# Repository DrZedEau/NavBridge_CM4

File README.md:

# NavBridge CM4

A Raspberry Pi Compute Module carrier board for BMW E-Series cars with the factory navigation system (E46, E39, E85 and similar).

The board plugs in between the car harness and the BMW MK3/MK4 navigation module. It brings Android Auto and Apple CarPlay to the factory display, buttons and audio, keeps the factory navigation, and needs no change to the car's wiring. It is made for [NavBridge App](https://github.com/DrZedEau/NavBridge_App), and also runs [LIVI](https://github.com/f-io/LIVI).

## Features

- **Video:** the Pi's picture on the factory display (analog RGB with sync on green), switched with the navigation module's picture from the factory buttons
- **Audio:** USB audio codec, with a stereo line output to the car's AUX or CD changer input and a microphone input
- **I-Bus:** an STM32 between the car and the navigation module turns the Pi on and off with the car, passes the factory buttons to the app and emulates a CD changer. It stays powered from the battery while the Pi is off.
- **Expansion:** two M.2 Key E slots (PCIe + USB, and USB), a USB-C host port for low-power devices (500 mA) and a CSI camera connector
- **CarPlay:** Apple MFi authentication coprocessor
- **Bench use:** a USB-C port to flash the Compute Module and power the board without the car. The MCU is updated from the Pi over USB.
- **Power:** automotive 5 V / 3.5 A buck converter on the fused, TVS-protected battery supply
- 100 × 100 mm, 4-layer PCB

Parts, connectors, pinouts, power and the revision history: [hardware/README.md](hardware/README.md).

## Compute Module

Raspberry Pi **CM4** or **CM5**, with **eMMC** (the board has no SD card slot) and **wireless**. The CM5 boots faster but needs a heatsink.

> [!WARNING]
> A CM4 needs a bootloader setting to turn its 3.3 V rail off at shutdown, otherwise the board keeps drawing from the car battery. See [Compute Module](documentation/README.md#compute-module).

## Documentation

| | |
|---|---|
| [Build and install guides](documentation/README.md) | [Make the navigation cable](documentation/NAV_CABLE.md), [flash the Compute Module](documentation/FLASH.md), [set up the Pi and flash the MCU](documentation/SETUP.md), [install the app](documentation/APP.md), [install in the car](documentation/NAV_CABLE.md#install-in-the-car) |
| [hardware/](hardware/README.md) | KiCad 10 project (revision 0.3), board details, revision history |
| [firmware/](firmware/README.md) | STM32C071 firmware: I-Bus, Pi power, video source, CSYNC, USB bootloader |
| [scripts/](scripts/README.md) | Raspberry Pi setup script and MCU flash script |
| [3D/](3D/README.md) | Printed case and connector housing (not added yet) |
| [images/](images/) | Pictures and renders |

## Project Status

Revision 0.3 adds the USB-C host port and fixes the issues found on the revision 0.2 prototypes, which work in the car with a small I-Bus fix (see [Revision history](hardware/README.md#revision-history)).

- [x] Schematic and PCB layout (revision 0.3)
- [x] Revision 0.2 prototypes built and tested in the car, with a CM4 and a CM5
- [ ] Revision 0.3 prototypes
- [ ] STM32 firmware: first version, being tested on the prototype
- [ ] Raspberry Pi setup script: first version
- [ ] 3D printed case and connector
- [ ] Testing on more BMW models

## Contributing

Bug reports, hardware improvements, firmware and documentation updates are welcome: open an issue or a pull request.

## License

Copyright 2026 DrZedEau

The hardware design — the KiCad project in `hardware/`, the 3D printed parts in `3D/` and the images in `images/` — is licensed under the **CERN Open Hardware Licence Version 2 – Strongly Reciprocal** (CERN-OHL-S-2.0), see [LICENSE](LICENSE). You may redistribute and modify it and make products from it under the terms of that licence. It is distributed without any express or implied warranty, including of merchantability, satisfactory quality and fitness for a particular purpose.

Source location: https://github.com/DrZedEau/NavBridge_CM4

As required by section 4 of the CERN-OHL-S, products made from this design must, where practicable, keep this source location visible.

The firmware in `firmware/` and the Raspberry Pi setup script in `scripts/` are licensed under the **GNU General Public License v2.0** (GPL-2.0), see [firmware/LICENSE](firmware/LICENSE) and [scripts/LICENSE](scripts/LICENSE). Third-party files keep their own licences.

## References

- CM5 NavBridge (previous board) https://github.com/DrZedEau/CM5_NavBridge
- NavBridge App https://github.com/DrZedEau/NavBridge_App
- LIVI project https://github.com/f-io/LIVI
- Raspberry Pi CM4 datasheet https://datasheets.raspberrypi.com/cm4/cm4-datasheet.pdf
- BMW Wiring Diagram System (WDS) https://bmwteka.com/wds/en/e85/e82460cf
- BMW On-Board Monitor documentation https://bmwteka.com/wds/en/e85/1b7f9876
- Community resources https://www.e46fanatics.com/threads/bmw-on-board-monitor-without-navigation-unit.1303552

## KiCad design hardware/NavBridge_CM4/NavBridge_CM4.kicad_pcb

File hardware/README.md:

# Hardware

The NavBridge CM4 board in detail: its parts, connectors, power, video and USB, and the KiCad project.

| Path | Content |
|---|---|
| `NavBridge_CM4/` | Revision 0.3 (current): schematics, PCB layout, project-local symbol, footprint and 3D model libraries |
| `NavBridge_CM4/production/` | JLCPCB fabrication files (Gerber archive, BOM, pick-and-place), made with the Fabrication Toolkit plugin |

Earlier revisions (0.1 and 0.2) are in the git history.

The project was made with **KiCad 10**. Open `NavBridge_CM4/NavBridge_CM4.kicad_pro`.

The project-local libraries only include the 3D models used on the board. The other models come from the standard KiCad library (`KICAD10_3DMODEL_DIR`, and `KICAD9_3DMODEL_DIR` for a few footprints).

## Board

- 100 × 100 mm, 4 copper layers, 1.6 mm
- 4 × M2.5 mounting holes at the corners (3 mm from each edge)
- 4 × M2.5 mounting holes for the Compute Module
- GND stitching vias around the board edge and across the ground pours
- Teardrops on vias and through-hole pads
- The battery fuse holder (FH1) takes a Littelfuse 0451003.MRL (3 A) fuse, fitted by hand after assembly
- No SD card slot: the Compute Module must have eMMC

## Main parts

| Function | Part |
|---|---|
| Compute Module connectors | 2 × Hirose DF40C-100DS (CN1, CN2), CM4 or CM5 |
| MCU | STM32C071 (U9) |
| I-Bus transceivers | 2 × ATA663231: car side (U8), navigation side (U10) |
| 5 V buck, from the car supply | LMR14030-Q1, 5 V / 3.5 A, automotive grade, switched on and off by the MCU |
| Battery protection | Fuse (FH1) and SMCJ24A TVS diode |
| Power muxes | 2 × TPS2117: 5 V from the buck or USB-C (U4), MCU 3.3 V from the LIN regulator or the CM (U11) |
| 3.3 V bucks | 2 × TPS54202, 2 A: USB hub, USB switches and video DAC (U5); M.2 slots and camera (U18) |
| Power switches | 2 × TPS2051B: audio codec; USB-C host port, 500 mA (U15) |
| USB hub | USB2514B, 4 ports |
| USB switches | 2 × TS3USB221: CM USB to the hub or to J1 (rpiboot); hub port 2 to CN6 or to J2 (U14) |
| Video DAC | ADV7125, 24-bit |
| RGB switch | TMUX1574 |
| Audio codec | PCM2912A: stereo line output, mono microphone input with bias |
| CarPlay authentication | Apple MFi343S00177, on I²C |

## Connectors

| Ref | Connector | Use |
|---|---|---|
| CN1, CN2 | Hirose DF40C-100DS | Raspberry Pi CM4 / CM5 |
| CN3 | Molex Micro-Fit 3.0, 12 pins (43045-1200) | To the navigation module |
| CN4 | 2 × 9 pin header, 2.54 mm, right angle | Car harness (X1313 connector) |
| CN5 | 2 × 5 pin header, 1.27 mm | STM32 SWD |
| CN6 | M.2 Key E | PCIe x1 + USB 2.0 module (the USB is shared with J2) |
| CN7 | M.2 Key E | USB 2.0 module |
| U1 | JST GH, 3 pins | Stereo line output |
| U2 | JST GH, 2 pins | Microphone input |
| U20 | 22-pin FPC, 0.5 mm (bottom side) | CSI camera (CAM1, 2 lanes) |
| J1 | USB-C | Raspberry Pi flashing and bench power |
| J2 | USB-C | USB 2.0 host port, 500 mA |

### CN4 – Car harness

| Pin | Signal | Pin | Signal |
|---|---|---|---|
| 1 | +BATT | 2 | GND |
| 3 | – | 4 | – |
| 5 | I-Bus | 6 | GND |
| 7 | – | 8 | – |
| 9 | Green out | 10 | GND |
| 11 | Blue out | 12 | GND |
| 13 | Red out | 14 | GND |
| 15 | – | 16 | – |
| 17 | Nav audio + | 18 | Nav audio − |

### CN3 – Navigation module

| Pin | Signal | Pin | Signal |
|---|---|---|---|
| 1 | GND | 7 | +BATT |
| 2 | GND | 8 | I-Bus (navigation side) |
| 3 | GND | 9 | Red in |
| 4 | GND | 10 | Green in |
| 5 | GND | 11 | Blue in |
| 6 | Nav audio − | 12 | Nav audio + |

+BATT and the navigation audio pass straight through between CN3 and CN4. The I-Bus does not: the car I-Bus (CN4 pin 5) and the navigation module's I-Bus (CN3 pin 8) each have their own ATA663231 transceiver, and the STM32 passes messages between them. The red, green and blue signals from the navigation module go through the RGB switch before reaching the display. The cable from CN3 to the navigation module is in [Make the navigation cable](../documentation/NAV_CABLE.md).

### Audio connectors

| Connector | Pin 1 | Pin 2 | Pin 3 |
|---|---|---|---|
| U2 (microphone) | MIC in | GND | |
| U1 (line out) | Left | GND | Right |

## Buttons and LEDs

| Silkscreen | Part | Function |
|---|---|---|
| nRPIBOOT | SW1 (slide switch) | Pulls the CM `nRPIBOOT` low and routes the CM USB port to the USB-C connector J1, for flashing with rpiboot |
| CN6 / USB-C | SW4 (slide switch) | Connects hub port 2 to M.2 slot CN6 (ON) or to the USB-C host port J2 (OFF) |
| RESET | SW2 | STM32 reset |
| BOOT | SW3 | STM32 BOOT0, to start the USB DFU bootloader |
| PWR | D2 (red) | CM power LED |
| ACT | D1 (green) | CM activity LED |
| STAT | D6 (yellow) | STM32 status LED |

The MCU can only be reflashed with the board powered from USB-C (J1). The BOOT button and the SWD connector's VTref both take their 3.3 V from the Compute Module.

## Power

```text
+BATT ─┬─ fuse ─ TVS ─ LMR14030 5 V buck (enabled by MCU) ─┐
       │                                                   ├─ TPS2117 ─ +5 V ─ CM and peripherals
       │                            USB-C (J1) 5 V ────────┘
       │
       ├─ diode ─ ATA663231 (car I-Bus) ─ 3.3 V ─┐
       │                                         ├─ TPS2117 ─ 3.3 V ─ STM32, RGB switch
       │                  CM 3.3 V output ───────┘
       │
       └─ diode ─ 1 kΩ ─ navigation I-Bus (LIN master termination)

+5 V ─ TPS54202 buck ─ 3.3 V ─ USB hub, USB switches, video DAC (through a ferrite bead)
+5 V ─ TPS54202 buck ─ 3.3 V ─ M.2 slots, camera
+5 V ─ TPS2051B switch ─ PCM2912A audio codec
+5 V ─ TPS2051B switch (500 mA) ─ USB-C host port (J2)
```

- The two TPS54202 converters and the two TPS2051B switches are enabled by the CM 3.3 V output, so they only run while the Compute Module is on.
- The TPS2117 selects between the car supply and USB-C automatically, so the board can be powered on the bench from USB-C alone. A divider on its `PR1` pin makes it switch to the car supply only once the buck output is above about 4.3 V, not while the buck is still starting up. The MCU's TPS2117 does the same with the LIN regulator, above about 2.5 V.
- The MCU is powered from the car battery through the car-side LIN transceiver's built-in 3.3 V regulator, so it keeps watching the I-Bus while the Raspberry Pi is off. It turns the 5 V buck on with the ignition, and off once the CM 3.3 V rail has gone away (see [firmware/README.md](../firmware/README.md)).
- A CM5 under heavy load, together with power-hungry M.2 or USB devices, can get close to the 3.5 A of the 5 V buck.

## I-Bus

- Two **ATA663231** LIN transceivers: one on the car I-Bus (U8), one on the navigation module's I-Bus (U10), with the STM32 in between. It forwards the frames both ways and sends them to the Pi over USB.
- LIN master termination (1 kΩ + diode, R24 and D7) on the navigation-side I-Bus, since the board is the only master on that segment.
- The car's wiring is not modified: the board plugs in between the car harness and the navigation module.

## Video

The Raspberry Pi drives the **ADV7125** video DAC through its 24-bit DPI interface. The STM32 combines the DPI `HSYNC` and `VSYNC` into a composite sync (`CSYNC`) with a hardware timer and feeds it to the DAC, which adds it to the green channel (RGsB) as the BMW display expects. So the board does not rely on the CM5's RP1 PIO for CSYNC, as the [CM5 NavBridge](https://github.com/DrZedEau/CM5_NavBridge) did.

The **TMUX1574** switch, controlled by the STM32, selects which picture reaches the display: the Raspberry Pi or the factory navigation module.

## USB

The CM USB 2.0 port goes through a **TS3USB221** switch controlled by the nRPIBOOT switch (SW1):

- **nRPIBOOT off** (normal use): CM → **USB2514B** hub:
  - port 1: M.2 slot CN7
  - port 2: M.2 slot CN6 or the USB-C host port (J2), through a second **TS3USB221** set by the CN6 / USB-C switch (SW4)
  - port 3: PCM2912A audio codec
  - port 4: STM32
- **nRPIBOOT on**: CM → USB-C connector (J1), to flash the eMMC with rpiboot

The USB-C host port (J2) supplies up to 500 mA through a **TPS2051B** current-limited switch and advertises default USB power (56 kΩ pull-ups on CC1/CC2). It is powered while the Compute Module is on and is meant for low-power devices, such as an analog video converter. When it is selected, M.2 slot CN6 has no USB, only PCIe.

The CM5's USB 3.0 ports are not used.

## Schematic sheets

| Sheet | Content |
|---|---|
| NavBridge_CM4 | CM4 / CM5 connectors, car connectors, audio connectors, LEDs, nRPIBOOT switch, mounting holes |
| Power | Battery input, LMR14030 5 V buck, USB-C connector (J1), TPS2117 power mux, TPS54202 3.3 V buck for the USB hub, the USB switches and the video DAC |
| MCU_Lin | STM32C071 MCU, two ATA663231 LIN transceivers (car I-Bus and navigation I-Bus), navigation I-Bus master termination, TPS2117 MCU power mux, SWD connector |
| Analog_RGB | ADV7125 video DAC and its supply filter, TMUX1574 RGB switch, 75 Ω termination |
| USB | USB2514B hub, TS3USB221 USB switch for rpiboot |
| USB-DFP | USB-C host port (J2), TS3USB221 switch between M.2 slot CN6 and J2 (set by SW4), TPS2051B 500 mA VBUS switch |
| Audio | PCM2912A USB audio codec and its power switch |
| M.2 | Two M.2 Key E slots, TPS54202 3.3 V buck |
| Misc | Apple MFi authentication coprocessor, CSI camera connector |
| SD_Card | Empty: the SD card slot was removed in revision 0.2 |

## Revision history

### 0.3 (current)

Not built yet. Changes from revision 0.2:

- **USB-C host port (J2)**, on the new USB-DFP sheet. A TS3USB221 (U14), set by the CN6 / USB-C slide switch (SW4), connects hub port 2 either to M.2 slot CN6 or to J2. VBUS comes from a TPS2051B (U15, 500 mA, on while the Compute Module is on), and 56 kΩ pull-ups on CC1/CC2 (R32, R33) advertise default USB power. The port is meant for low-power devices, such as an analog video converter.
- **3.3 V for the USB hub, the USB switches and the video DAC** now comes from a TPS54202 buck (U5) instead of the TLV75533 LDO.
- **M.2 3.3 V buck:** TPS54202 (U18) instead of the AP63203.
- **Video DAC supply:** an extra 22 µF after the ferrite bead, which lowers and damps the resonance of the bead and capacitor filter.
- **Navigation I-Bus master termination** on the board: D7 (1N4148W) and R24 (1 kΩ, 1206) from +BATT to IBUS_NAV, next to U10. This replaces the revision 0.2 bodge (see below).
- **MCU power mux (U11):** R25 (150 kΩ) and R26 (100 kΩ) divide `+3V3_LIN_REG` onto `PR1`, so U11 only selects the LIN regulator above about 2.5 V (see below).
- **Main power mux (U4):** R10 (330 kΩ) and R11 (100 kΩ) divide `+5V_BUCK` onto `PR1`, so U4 only switches to the car supply once the buck output is above about 4.3 V. With `PR1` tied straight to `VIN1`, as on revision 0.2, and USB-C and the car supply both connected, U4 would switch to the buck at about 1 V while it starts up, and stay on it while it decays at turn-off.
- **BOOT button (SW3):** now pulls BOOT0 up from the CM 3.3 V rail (`+3V3`) instead of the MCU rail (`+3V3_MUX`). The MCU can only be reflashed with the board powered from USB-C (J1).
- The auxiliary 5 V connector (CN8) was removed.
- More GND stitching vias, and teardrops on vias and through-hole pads.

### 0.2

First CM4 revision. The prototypes work in the car with the I-Bus bodge below.

## Known issues on revision 0.2

Both are fixed in revision 0.3.

### Navigation-side I-Bus has no master termination

The board splits the I-Bus in two: the car side (U8, CN4 pin 5) keeps the car's own termination, but the navigation side (U10 pin 6 to CN3 pin 8) only has U10's internal 30 kΩ slave pull-up. That cannot drive the navigation module's input at 9600 baud: in the car, every byte sent to it came back distorted, while with CN3 unplugged the same frames went through cleanly.

- **Bodge on revision 0.2:** a 1 kΩ resistor (1/4 W) in series with a 1N4148 diode between CN3 pin 7 (+BATT, diode anode) and CN3 pin 8 (navigation I-Bus, resistor end), on the back of the connector. This is the standard LIN master termination; it draws at most 12 mA while the bus is low.
- **Revision 0.3:** the same 1 kΩ + diode (R24, D7) from +BATT to IBUS_NAV, next to U10. The car side needs nothing.
  - The ATA663231 datasheet (DS20006075E, Figure 1-14 "Typical Application Circuit SBC") shows exactly this as the "Commander node pull up": R2 = 1 kΩ in series with diode D2, from VBAT to LIN. It gives no package or power rating. With the bus held low the resistor takes about 0.2 W at 14 V, and up to about 0.75 W at 28 V (the datasheet's 2-minute VS rating), hence the 1206 (0.25 W) resistor. The diode must be rated above the 40 V LIN/VS maximum (BAS16, 1N4148W).
  - The same figure also has C2 = 220 pF from LIN to GND. Neither revision has it on IBUS_CAR or IBUS_NAV: the I-Bus works without it, and it would only add EMC filtering.

The firmware's `STATUS` line shows the effect (`ibus2` `tx` counting up, `col` and `err` staying put), see [firmware/README.md](../firmware/README.md#usb).

### The MCU's power mux can be captured by a back-powered LIN regulator

On revision 0.2, U11 (TPS2117) has `PR1` tied to `VIN1` = `+3V3_LIN_REG`, so it switches the MCU to the car-side ATA663231's regulator as soon as that rail rises above about 1 V. Without 12 V (USB-C only), anything that drives or pulls up U8's `EN`, `TXD` or `RXD` feeds that rail through U8's protection diodes, and the MCU browns out in a loop. The firmware works around it (LIN pins floating until U8 is known to be powered).

Revision 0.3 adds a divider on `PR1` (R25, R26), so U11 only selects `VIN1` above about 2.5 V. The back-fed rail measured about 1.5 V on revision 0.2.

## Other notes for the next revision

- **Pi access to the MCU's SWD:** routing SWDIO, SWCLK and NRST to spare CM GPIOs (through a buffer or switch powered from the CM 3.3 V, so the MCU's SWD pull-ups cannot feed the CM while it is off) would let the Pi program and recover the MCU with OpenOCD, without a debugger.
- **PA10 (RGB select) is also USART1 RX** for ST's ROM bootloader, and its 10 kΩ pull-down holds it low. It only matters if ST's ROM bootloader is to be used on a programmed chip; the NavBridge bootloader does not need it.

## License

CERN-OHL-S-2.0, see [LICENSE](../LICENSE).

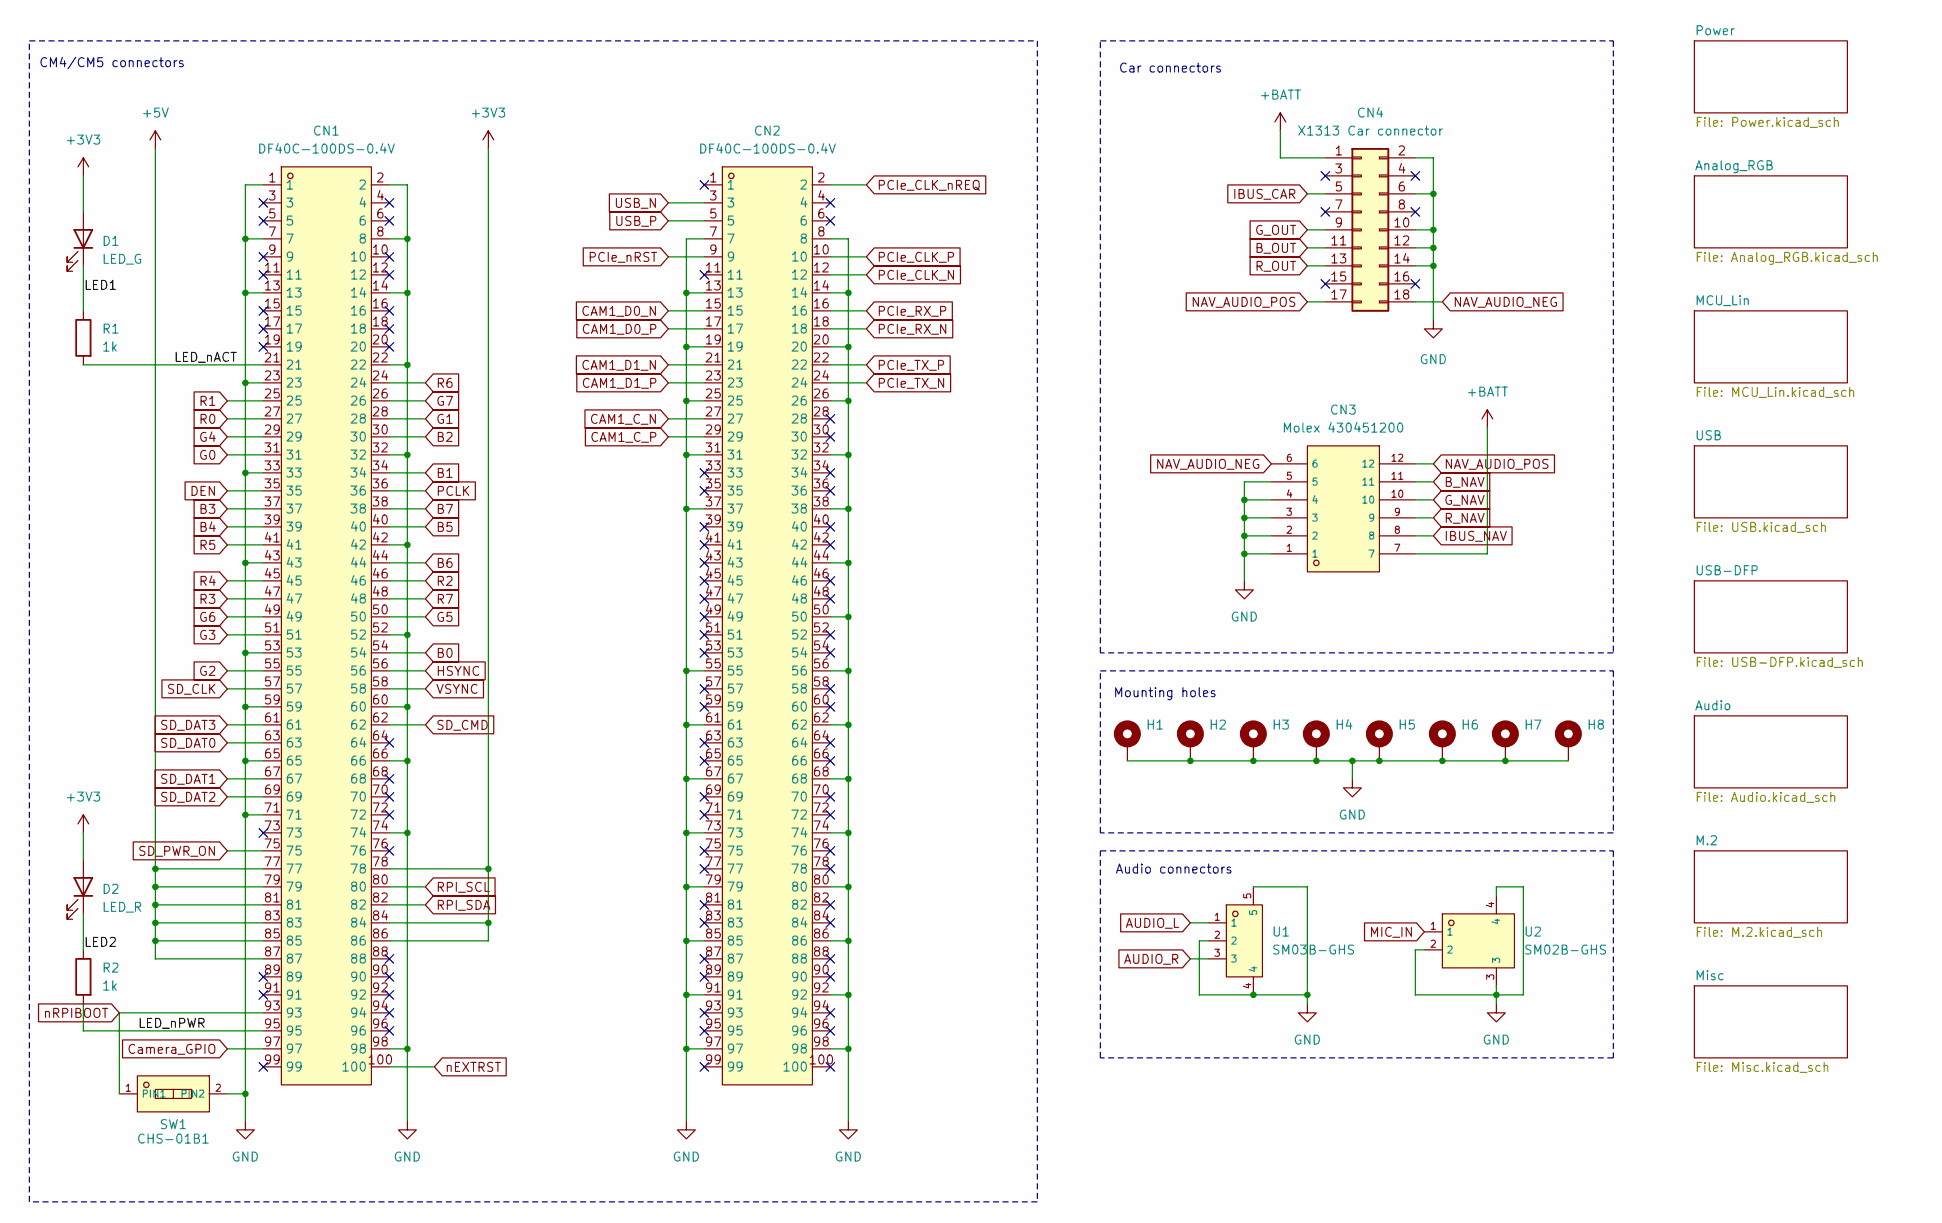
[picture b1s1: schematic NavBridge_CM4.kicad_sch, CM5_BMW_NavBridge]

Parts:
CN1, CN2: DF40C-100DS-0.4V; Hirose_DF40C-100DS-0.4V_2x50_P0.4mm; LCSC Part C597931
CN3: Molex 430451200; C277636_CONN-TH_12P-P3_00-S3_00_L12_2-W21_7-EH10_7; LCSC C277636
CN4: X1313 Car connector; PinHeader_2x09_P2.54mm_Horizontal; LCSC C492437
D1: LED_G; LED_0805_2012Metric; LCSC C2297
D2: LED_R; LED_0805_2012Metric; LCSC C84256
H1, H2, H3, H4, H5, H6, H7, H8: MountingHole_Pad; MountingHole_2.7mm_M2.5_Pad_TopBottom
R1, R2: 1k; R_0402_1005Metric; LCSC C11702
SW1: CHS-01B1; C3312309_SW-SMD_NIDEC_CHS-01B1; LCSC C3312309
U1: SM03B-GHS; C514175_CONN-TH_SM03B-GHS-TB-LF-SN; LCSC C514175
U2: SM02B-GHS; C189893_CONN-SMD_SM02B-GHS-TB-LF-SN; LCSC C189893

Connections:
+3V3: CN1.78, CN1.84, CN1.86, D1.2 (A), D2.2 (A); also elsewhere on the board
+5V: CN1.77, CN1.79, CN1.81, CN1.83, CN1.85, CN1.87; also elsewhere on the board
+BATT: CN3.7, CN4.1; also elsewhere on the board
/LED1: D1.1 (K), R1.1
/LED2: D2.1 (K), R2.1
/LED_nACT: CN1.21, R1.2
/LED_nPWR: CN1.95, R2.2
AUDIO_L: U1.1; also elsewhere on the board
AUDIO_R: U1.3; also elsewhere on the board
B0: CN1.54; also elsewhere on the board
B1: CN1.34; also elsewhere on the board
B2: CN1.30; also elsewhere on the board
B3: CN1.37; also elsewhere on the board
B4: CN1.39; also elsewhere on the board
B5: CN1.40; also elsewhere on the board
B6: CN1.44; also elsewhere on the board
B7: CN1.38; also elsewhere on the board
B_NAV: CN3.11; also elsewhere on the board
B_OUT: CN4.11; also elsewhere on the board
CAM1_C_N: CN2.27; also elsewhere on the board
CAM1_C_P: CN2.29; also elsewhere on the board
CAM1_D0_N: CN2.15; also elsewhere on the board
CAM1_D0_P: CN2.17; also elsewhere on the board
CAM1_D1_N: CN2.21; also elsewhere on the board
CAM1_D1_P: CN2.23; also elsewhere on the board
Camera_GPIO: CN1.97; also elsewhere on the board
DEN: CN1.35; also elsewhere on the board
G0: CN1.31; also elsewhere on the board
G1: CN1.28; also elsewhere on the board
G2: CN1.55; also elsewhere on the board
G3: CN1.51; also elsewhere on the board
G4: CN1.29; also elsewhere on the board
G5: CN1.50; also elsewhere on the board
G6: CN1.49; also elsewhere on the board
G7: CN1.26; also elsewhere on the board
GND: CN1.1, CN1.2, CN1.7, CN1.8, CN1.13, CN1.14, CN1.22, CN1.23, CN1.32, CN1.33, CN1.42, CN1.43, CN1.52, CN1.53, CN1.59, CN1.60, CN1.65, CN1.66, CN1.71, CN1.74, CN1.98, CN2.7, CN2.8, CN2.13, CN2.14, CN2.19, CN2.20, CN2.25, CN2.26, CN2.31, CN2.32, CN2.37, CN2.38, CN2.44, CN2.50, CN2.55, CN2.56, CN2.61, CN2.62, CN2.67, CN2.68, CN2.73, CN2.74, CN2.79, CN2.80, CN2.85, CN2.86, CN2.91, CN2.92, CN2.97, CN2.98, CN3.1, CN3.2, CN3.3, CN3.4, CN3.5, CN4.2, CN4.6, CN4.10, CN4.12, CN4.14, H1.1 (1_1), H2.1 (1_1), H3.1 (1_1), H4.1 (1_1), H5.1 (1_1), H6.1 (1_1), H7.1 (1_1), H8.1 (1_1), SW1.2 (PIN2), U1.2, U1.4, U1.5, U2.2, U2.3, U2.4; also elsewhere on the board
G_NAV: CN3.10; also elsewhere on the board
G_OUT: CN4.9; also elsewhere on the board
HSYNC: CN1.56; also elsewhere on the board
IBUS_CAR: CN4.5; also elsewhere on the board
IBUS_NAV: CN3.8; also elsewhere on the board
MIC_IN: U2.1; also elsewhere on the board
NAV_AUDIO_NEG: CN3.6, CN4.18
NAV_AUDIO_POS: CN3.12, CN4.17
PCIe_CLK_N: CN2.12; also elsewhere on the board
PCIe_CLK_P: CN2.10; also elsewhere on the board
PCIe_CLK_nREQ: CN2.2; also elsewhere on the board
PCIe_RX_N: CN2.18; also elsewhere on the board
PCIe_RX_P: CN2.16; also elsewhere on the board
PCIe_TX_N: CN2.24; also elsewhere on the board
PCIe_TX_P: CN2.22; also elsewhere on the board
PCIe_nRST: CN2.9; also elsewhere on the board
PCLK: CN1.36; also elsewhere on the board
R0: CN1.27; also elsewhere on the board
R1: CN1.25; also elsewhere on the board
R2: CN1.46; also elsewhere on the board
R3: CN1.47; also elsewhere on the board
R4: CN1.45; also elsewhere on the board
R5: CN1.41; also elsewhere on the board
R6: CN1.24; also elsewhere on the board
R7: CN1.48; also elsewhere on the board
RPI_SCL: CN1.80; also elsewhere on the board
RPI_SDA: CN1.82; also elsewhere on the board
R_NAV: CN3.9; also elsewhere on the board
R_OUT: CN4.13; also elsewhere on the board
SD_CLK: CN1.57
SD_CMD: CN1.62
SD_DAT0: CN1.63
SD_DAT1: CN1.67
SD_DAT2: CN1.69
SD_DAT3: CN1.61
SD_PWR_ON: CN1.75
USB_N: CN2.3; also elsewhere on the board
USB_P: CN2.5; also elsewhere on the board
VSYNC: CN1.58; also elsewhere on the board
nEXTRST: CN1.100; also elsewhere on the board
nRPIBOOT: CN1.93, SW1.1 (PIN1); also elsewhere on the board

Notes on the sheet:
Car connectors
Audio connectors
CM4/CM5 connectors
Mounting holes

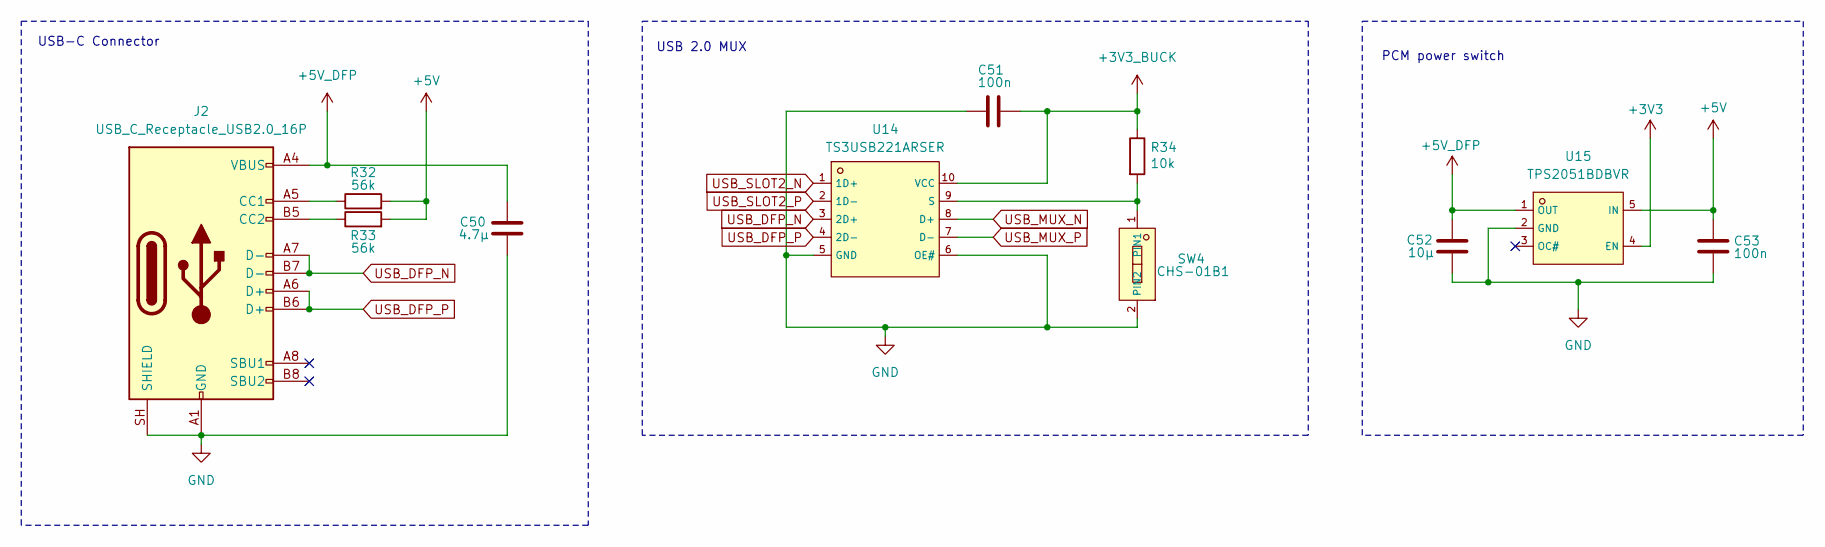
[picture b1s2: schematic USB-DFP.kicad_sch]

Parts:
C50: 4.7µ; C_0805_2012Metric; LCSC C1779
C51, C53: 100n; C_0402_1005Metric; LCSC C307331
C52: 10µ; C_0805_2012Metric; LCSC C15850
J2: USB_C_Receptacle_USB2.0_16P; USB_C_Receptacle_G-Switch_GT-USB-7010ASV; LCSC C2988369
R32, R33: 56k; R_0402_1005Metric; LCSC C25796
R34: 10k; R_0402_1005Metric; LCSC C25744
SW4: CHS-01B1; C3312309_SW-SMD_NIDEC_CHS-01B1; LCSC C3312309
U14: TS3USB221ARSER; C128396_UQFN-10_L2_0-W1_5-P0_50-BL; LCSC C128396
U15: TPS2051BDBVR; C24593_SOT-23-5_L3_0-W1_7-P0_95-LS2_8-BR; LCSC C24593

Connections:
+3V3: U15.4 (EN); also elsewhere on the board
+3V3_BUCK: C51.2, R34.1, U14.10 (VCC); also elsewhere on the board
+5V: C53.1, R32.2, R33.2, U15.5 (IN); also elsewhere on the board
+5V_DFP: C50.2, C52.2, J2.A4 (VBUS), J2.A9 (VBUS), J2.B4 (VBUS), J2.B9 (VBUS), U15.1 (OUT)
GND: C50.1, C51.1, C52.1, C53.2, J2.A1 (GND), J2.A12 (GND), J2.B1 (GND), J2.B12 (GND), J2.SH (SHIELD), SW4.2 (PIN2), U14.5 (GND), U14.6 (OE#), U15.2 (GND); also elsewhere on the board
unnamed: J2.A5 (CC1), R32.1
unnamed: J2.B5 (CC2), R33.1
unnamed: R34.2, SW4.1 (PIN1), U14.9 (S)
USB_DFP_N: J2.A7 (D-), J2.B7 (D-), U14.3 (2D+)
USB_DFP_P: J2.A6 (D+), J2.B6 (D+), U14.4 (2D-)
USB_MUX_N: U14.8 (D+); also elsewhere on the board
USB_MUX_P: U14.7 (D-); also elsewhere on the board
USB_SLOT2_N: U14.1 (1D+); also elsewhere on the board
USB_SLOT2_P: U14.2 (1D-); also elsewhere on the board

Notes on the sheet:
PCM power switch
USB-C Connector
USB 2.0 MUX

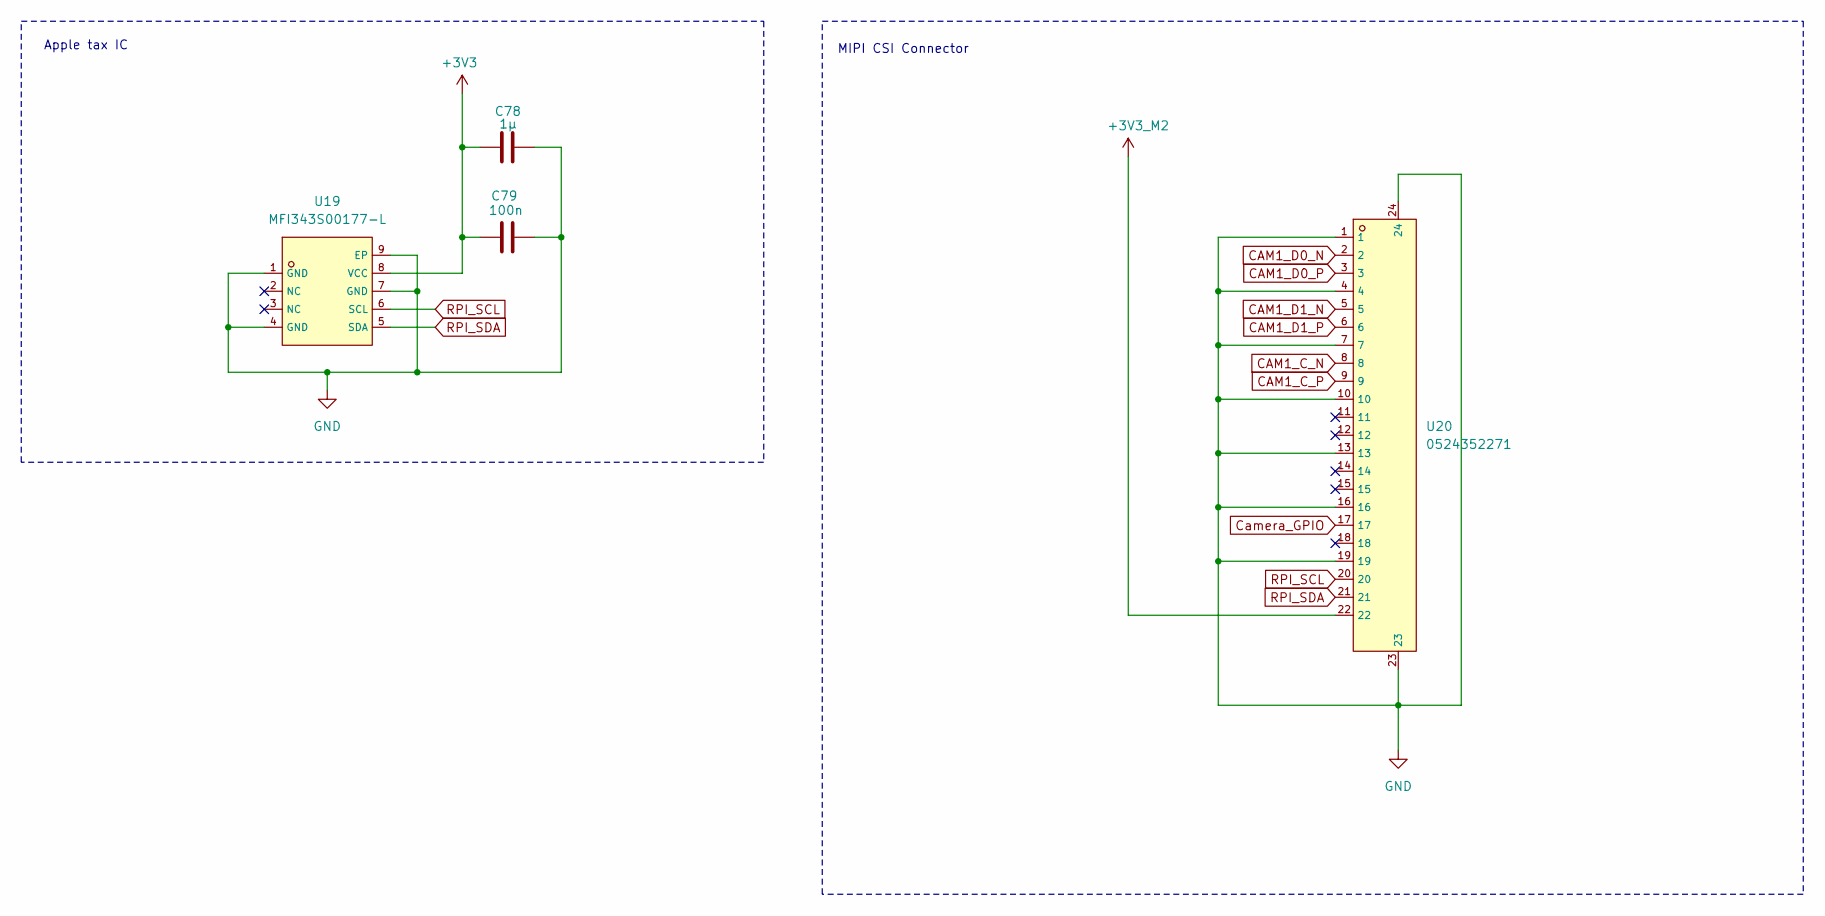
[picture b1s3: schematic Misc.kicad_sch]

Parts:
C78: 1µ; C_0402_1005Metric; LCSC C52923
C79: 100n; C_0402_1005Metric; LCSC C307331
U19: MFI343S00177-L; C33770534_DFN-8_L3_0-W2_0-P0_50-BL-EP1_6; LCSC C33770534
U20: 0524352271; C5468341_FPC-SMD_22P-P0_50_0524352271; LCSC C5468341

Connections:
+3V3: C78.1, C79.1, U19.8 (VCC); also elsewhere on the board
+3V3_M2: U20.22; also elsewhere on the board
CAM1_C_N: U20.8; also elsewhere on the board
CAM1_C_P: U20.9; also elsewhere on the board
CAM1_D0_N: U20.2; also elsewhere on the board
CAM1_D0_P: U20.3; also elsewhere on the board
CAM1_D1_N: U20.5; also elsewhere on the board
CAM1_D1_P: U20.6; also elsewhere on the board
Camera_GPIO: U20.17; also elsewhere on the board
GND: C78.2, C79.2, U19.1 (GND), U19.4 (GND), U19.7 (GND), U19.9 (EP), U20.1, U20.4, U20.7, U20.10, U20.13, U20.16, U20.19, U20.23, U20.24; also elsewhere on the board
RPI_SCL: U19.6 (SCL), U20.20; also elsewhere on the board
RPI_SDA: U19.5 (SDA), U20.21; also elsewhere on the board

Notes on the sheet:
Apple tax IC
MIPI CSI Connector

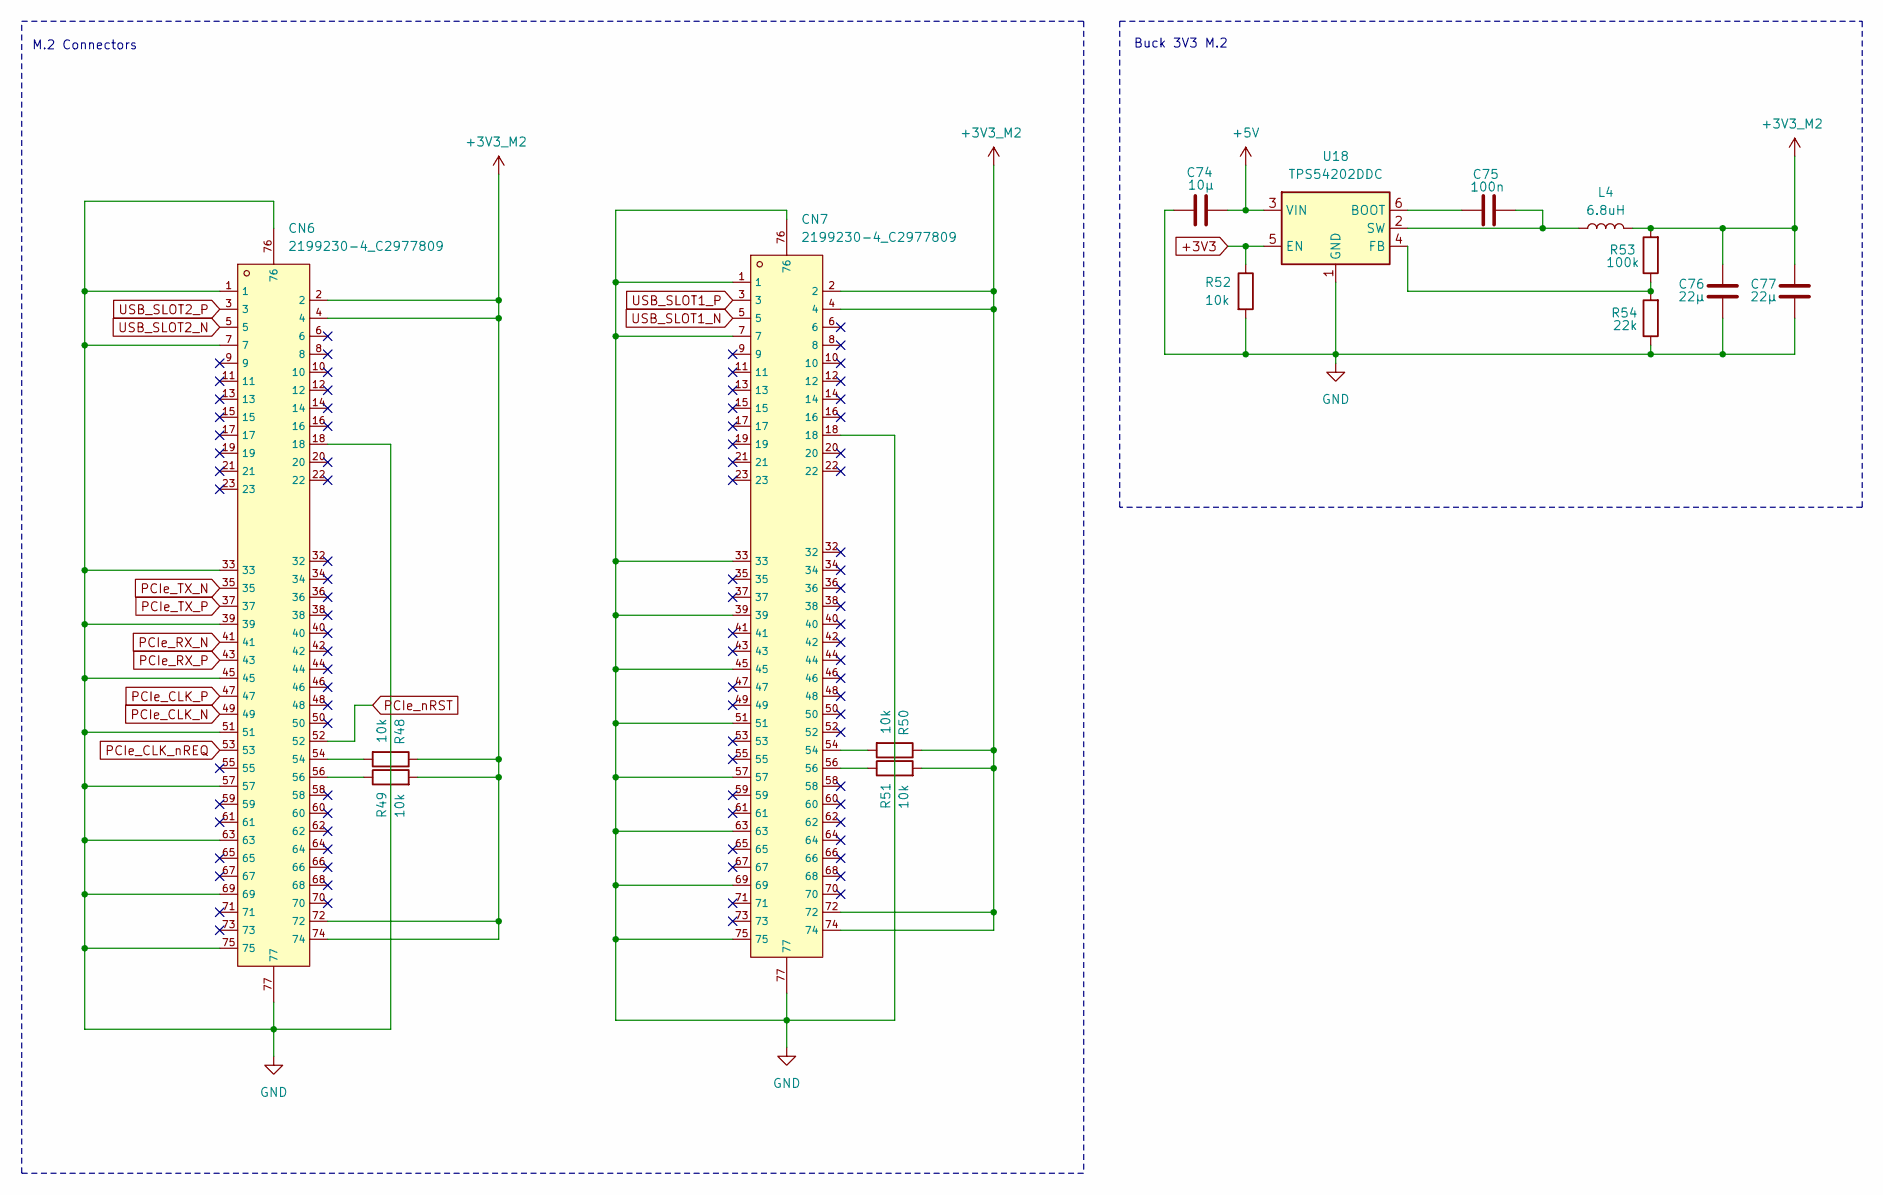
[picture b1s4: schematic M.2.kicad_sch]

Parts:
C74: 10µ; C_0805_2012Metric; LCSC C15850
C75: 100n; C_0402_1005Metric; LCSC C307331
C76, C77: 22µ; C_1206_3216Metric; LCSC C12891
CN6, CN7: 2199230-4_C2977809; C2977809_PCIE-SMD_2199230-4; LCSC C2977809
L4: 6.8uH; L_Sunlord_MWSA0518S; LCSC C2928918
R48, R49, R50, R51, R52: 10k; R_0402_1005Metric; LCSC C25744
R53: 100k; R_0402_1005Metric; LCSC C25741
R54: 22k; R_0402_1005Metric; LCSC C25768
U18: TPS54202DDC; SOT-23-6; LCSC C191884

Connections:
+3V3: R52.1, U18.5 (EN); also elsewhere on the board
+3V3_M2: C76.1, C77.1, CN6.2, CN6.4, CN6.72, CN6.74, CN7.2, CN7.4, CN7.72, CN7.74, L4.2, R48.1, R49.2, R50.1, R51.2, R53.2; also elsewhere on the board
+5V: C74.2, U18.3 (VIN); also elsewhere on the board
GND: C74.1, C76.2, C77.2, CN6.1, CN6.7, CN6.18, CN6.33, CN6.39, CN6.45, CN6.51, CN6.57, CN6.63, CN6.69, CN6.75, CN6.76, CN6.77, CN7.1, CN7.7, CN7.18, CN7.33, CN7.39, CN7.45, CN7.51, CN7.57, CN7.63, CN7.69, CN7.75, CN7.76, CN7.77, R52.2, R54.1, U18.1 (GND); also elsewhere on the board
unnamed: CN6.54, R48.2
unnamed: CN6.56, R49.1
unnamed: CN7.54, R50.2
unnamed: CN7.56, R51.1
unnamed: C75.2, U18.6 (BOOT)
unnamed: R53.1, R54.2, U18.4 (FB)
unnamed: C75.1, L4.1, U18.2 (SW)
PCIe_CLK_N: CN6.49; also elsewhere on the board
PCIe_CLK_P: CN6.47; also elsewhere on the board
PCIe_CLK_nREQ: CN6.53; also elsewhere on the board
PCIe_RX_N: CN6.41; also elsewhere on the board
PCIe_RX_P: CN6.43; also elsewhere on the board
PCIe_TX_N: CN6.35; also elsewhere on the board
PCIe_TX_P: CN6.37; also elsewhere on the board
PCIe_nRST: CN6.52; also elsewhere on the board
USB_SLOT1_N: CN7.5; also elsewhere on the board
USB_SLOT1_P: CN7.3; also elsewhere on the board
USB_SLOT2_N: CN6.5; also elsewhere on the board
USB_SLOT2_P: CN6.3; also elsewhere on the board

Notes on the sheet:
M.2 Connectors
Buck 3V3 M.2

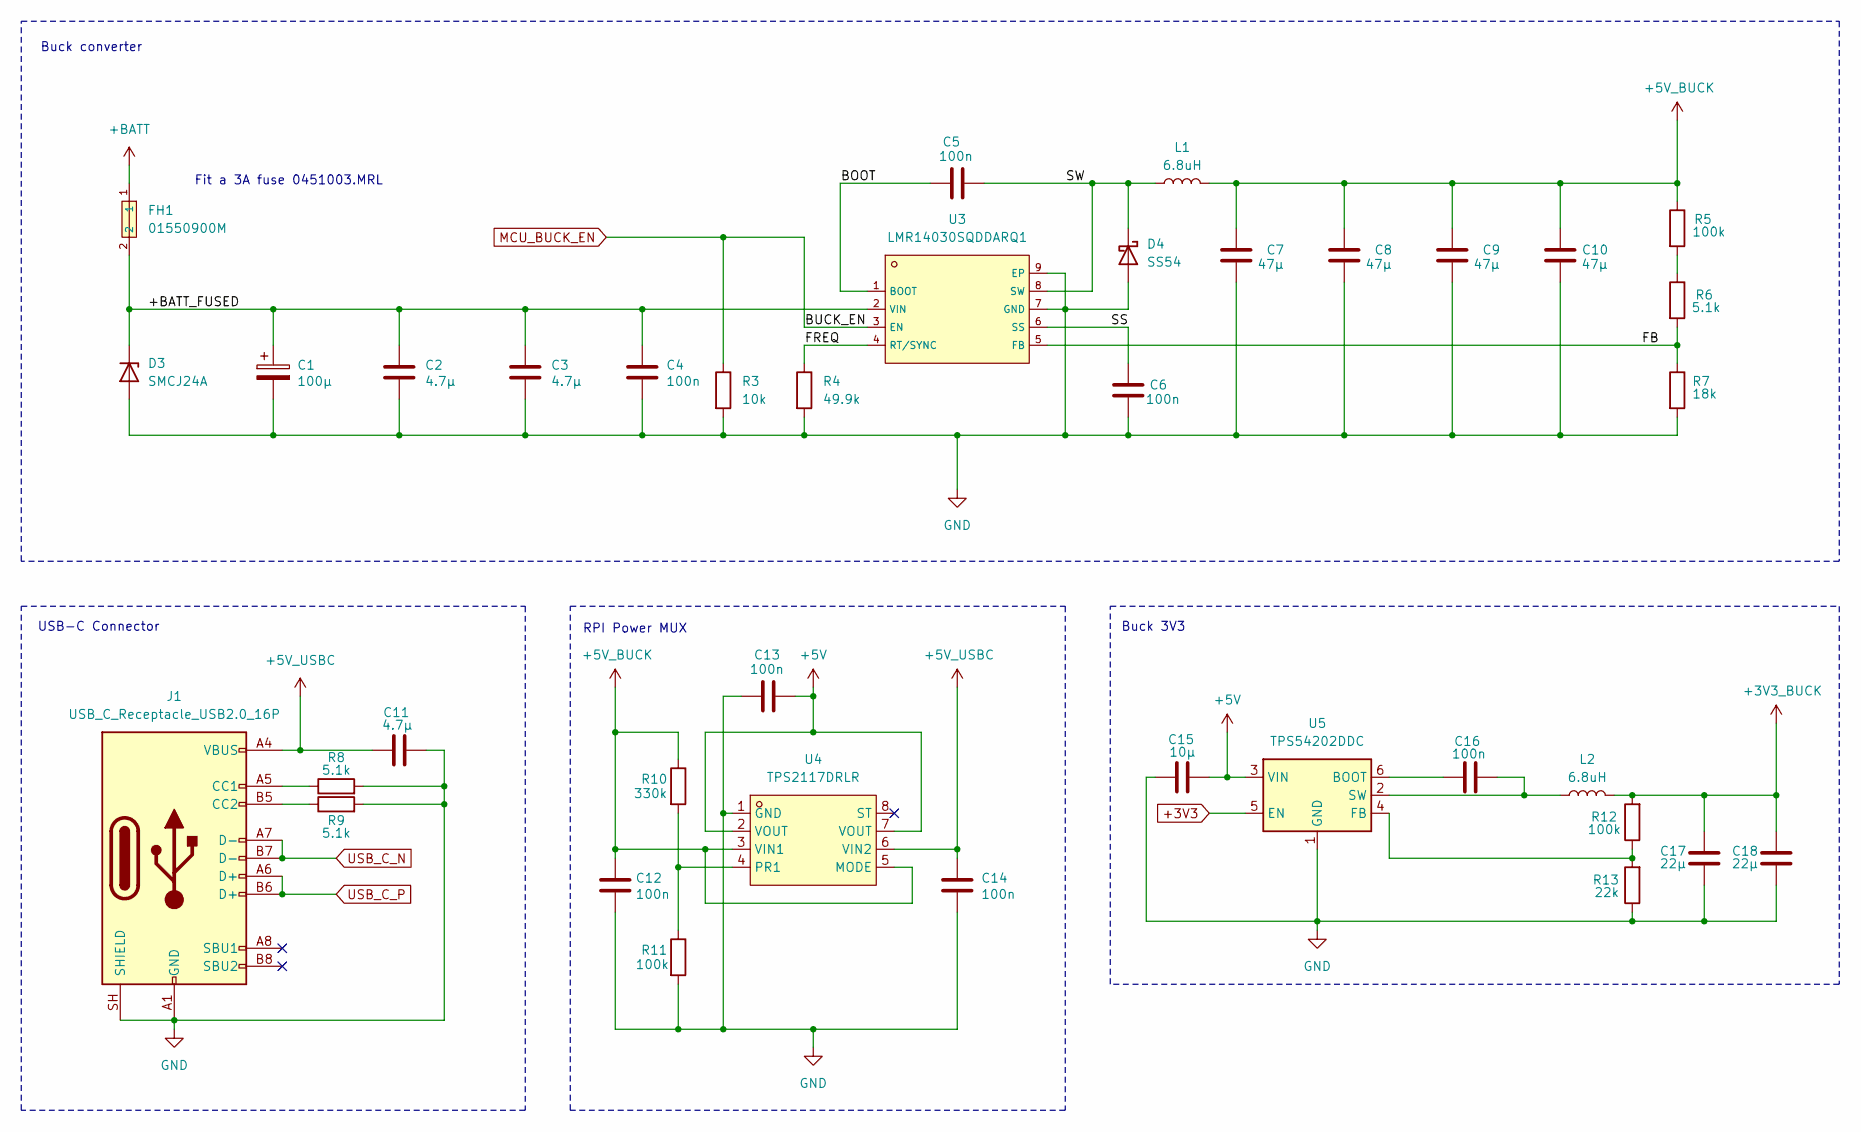
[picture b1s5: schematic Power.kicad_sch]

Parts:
C1: 100µ; CP_Elec_6.3x5.8; LCSC C128464
C2, C3: 4.7µ; C_1206_3216Metric; LCSC C29823
C4, C5, C6, C12, C13, C14, C16: 100n; C_0402_1005Metric; LCSC C307331
C7, C8, C9, C10: 47µ; C_1206_3216Metric; LCSC C96123
C11: 4.7µ; C_0805_2012Metric; LCSC C1779
C15: 10µ; C_0805_2012Metric; LCSC C15850
C17, C18: 22µ; C_1206_3216Metric; LCSC C12891
D3: SMCJ24A; D_SMC; LCSC C19077604
D4: SS54; D_SMA; LCSC C22452
FH1: 01550900M; C108518_FUSE-SMD_L9_8-W5_0_01550900M; LCSC C108518
J1: USB_C_Receptacle_USB2.0_16P; USB_C_Receptacle_G-Switch_GT-USB-7010ASV; LCSC C2988369
L1: 6.8uH; L_Sunlord_MWSA1003S; LCSC C2453947
L2: 6.8uH; L_Sunlord_MWSA0518S; LCSC C2928918
R3: 10k; R_0402_1005Metric; LCSC C25744
R4: 49.9k; R_0402_1005Metric; LCSC C25897
R5, R11, R12: 100k; R_0402_1005Metric; LCSC C25741
R6, R8, R9: 5.1k; R_0402_1005Metric; LCSC C25905
R7: 18k; R_0402_1005Metric; LCSC C25762
R10: 330k; R_0402_1005Metric; LCSC C25778
R13: 22k; R_0402_1005Metric; LCSC C25768
U3: LMR14030SQDDARQ1; C485817_SO-8_L4_9-W3_9-P1_27-LS6_0-BL-EP; LCSC C485817
U4: TPS2117DRLR; C22399676_SOT-583-8_L2_1-W1_2-P0_50-LS1_6-BL; LCSC Part C22399676
U5: TPS54202DDC; SOT-23-6; LCSC C191884

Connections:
+3V3: U5.5 (EN); also elsewhere on the board
+3V3_BUCK: C17.1, C18.1, L2.2, R12.2; also elsewhere on the board
+5V: C13.2, C15.2, U4.2 (VOUT), U4.7 (VOUT), U5.3 (VIN); also elsewhere on the board
+5V_BUCK: C7.1, C8.1, C9.1, C10.1, C12.1, L1.2, R5.1, R10.1, U4.3 (VIN1), U4.5 (MODE)
+5V_USBC: C11.1, C14.1, J1.A4 (VBUS), J1.A9 (VBUS), J1.B4 (VBUS), J1.B9 (VBUS), U4.6 (VIN2)
+BATT: FH1.1; also elsewhere on the board
/Power/+BATT_FUSED: C1.1, C2.1, C3.1, C4.1, D3.1 (K), FH1.2, U3.2 (VIN)
/Power/BOOT: C5.1, U3.1 (BOOT)
/Power/FB: R6.2, R7.1, U3.5 (FB)
/Power/FREQ: R4.1, U3.4 (RT/SYNC)
/Power/SS: C6.1, U3.6 (SS)
/Power/SW: C5.2, D4.1 (K), L1.1, U3.8 (SW)
GND: C1.2, C2.2, C3.2, C4.2, C6.2, C7.2, C8.2, C9.2, C10.2, C11.2, C12.2, C13.1, C14.2, C15.1, C17.2, C18.2, D3.2 (A), D4.2 (A), J1.A1 (GND), J1.A12 (GND), J1.B1 (GND), J1.B12 (GND), J1.SH (SHIELD), R3.2, R4.2, R7.2, R8.2, R9.2, R11.2, R13.1, U3.7 (GND), U3.9 (EP), U4.1 (GND), U5.1 (GND); also elsewhere on the board
MCU_BUCK_EN: R3.1, U3.3 (EN); also elsewhere on the board
unnamed: J1.A5 (CC1), R8.1
unnamed: J1.B5 (CC2), R9.1
unnamed: R5.2, R6.1
unnamed: R10.2, R11.1, U4.4 (PR1)
unnamed: C16.2, U5.6 (BOOT)
unnamed: R12.1, R13.2, U5.4 (FB)
unnamed: C16.1, L2.1, U5.2 (SW)
USB_C_N: J1.A7 (D-), J1.B7 (D-); also elsewhere on the board
USB_C_P: J1.A6 (D+), J1.B6 (D+); also elsewhere on the board

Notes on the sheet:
Buck converter
Fit a 3A fuse 0451003.MRL
USB-C Connector
RPI Power MUX
Buck 3V3
